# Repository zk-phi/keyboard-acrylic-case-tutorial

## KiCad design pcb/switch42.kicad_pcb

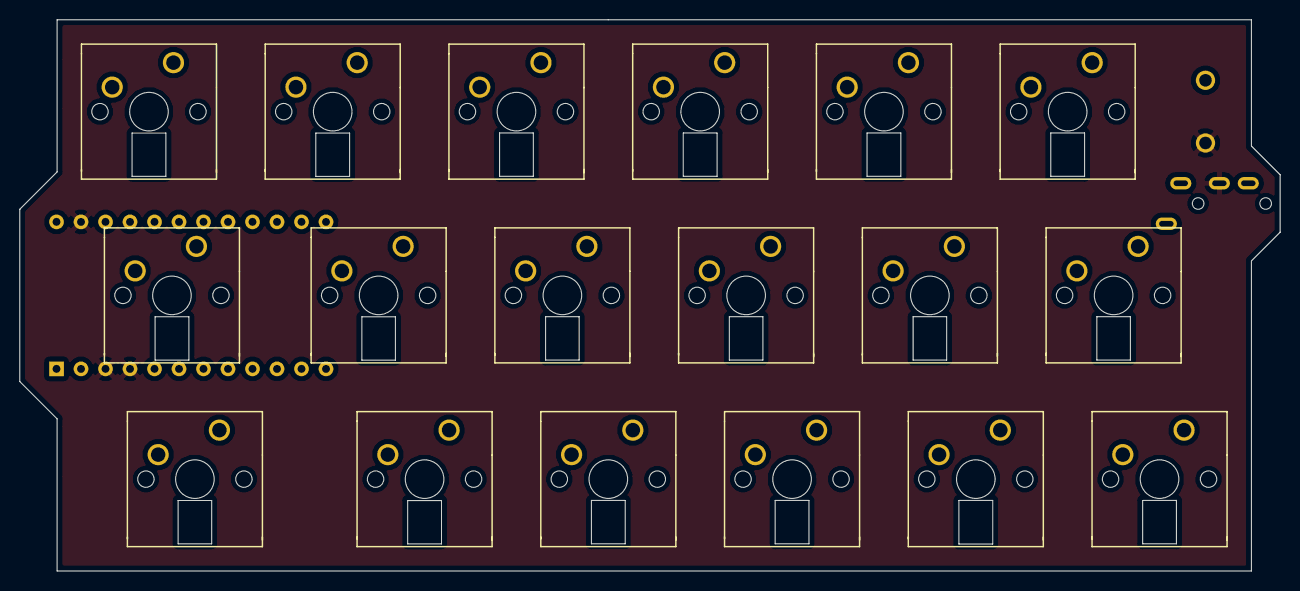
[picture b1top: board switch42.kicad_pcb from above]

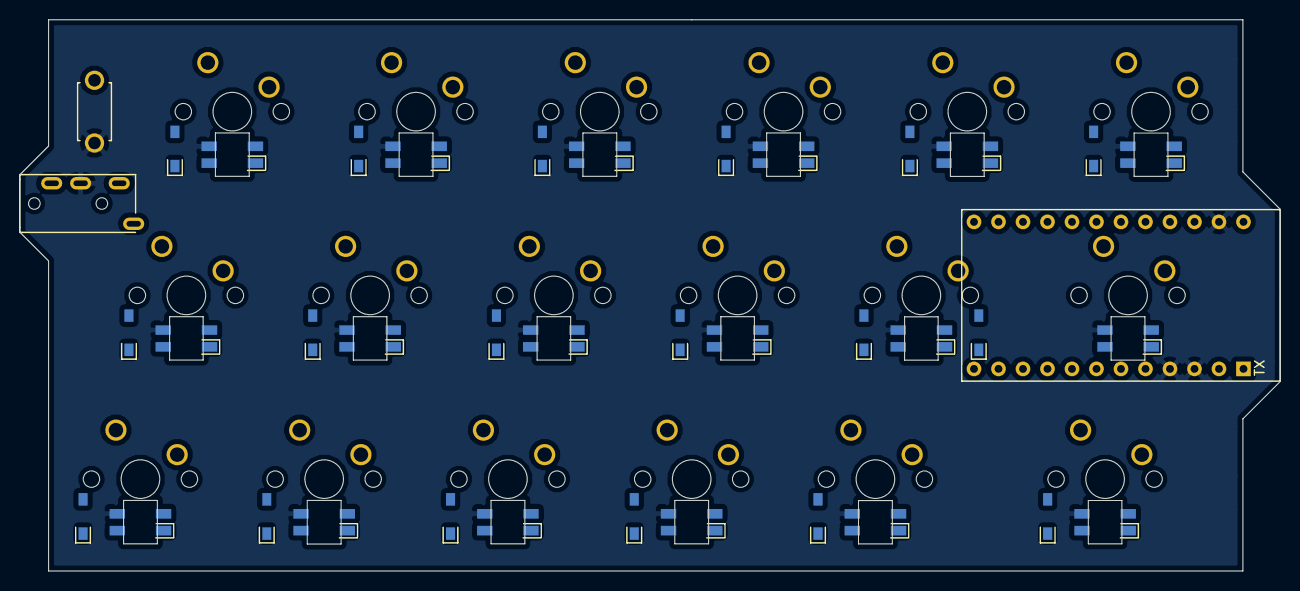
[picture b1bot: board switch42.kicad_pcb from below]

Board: 2 copper layers, 130.7 x 57.1 mm, 57 parts (21 on the bottom side), 49 nets, no tracks yet.

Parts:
D1, D2, D3, D4, D5, D6, D7, D8, D9, D10, D11, D12, D14, D15, D16, D18, D19, D20: D; D_SMD-irreversible
J1: MJ-4PP-9; MJ-4PP-9-irreversible
L1, L2, L3, L4, L5, L6, L7, L8, L9, L10, L11, L12, L14, L15, L16, L18, L19, L20: SK6812MINI; SK6812MINI-irreversible
SW1: SW_PUSH; ResetSW-irreversible
SW2, SW5, SW6, SW7, SW8, SW9, SW10, SW11, SW12, SW13, SW15, SW16, SW17, SW19, SW20, SW21: SW_PUSH; MX_1.00u-irreversible
SW3: SW_PUSH; MX_1.25u-irreversible
SW4: SW_PUSH; MX_1.50u-irreversible
U1: ProMicro; ProMicro_Reversed_Conthrough-irreversible

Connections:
GND: J1.C, L1.2, L2.2, L3.2, L4.2, L5.2, L6.2, L7.2, L8.2, L9.2, L10.2, L11.2, L12.2, L14.2, L15.2, L16.2, L18.2, L19.2, L20.2, SW1.2, U1.3, U1.4, U1.23
unnamed: D1.2, SW2.2
unnamed: D2.2, SW3.2
unnamed: D3.2, SW4.2
unnamed: D4.2, SW5.2
unnamed: D5.2, SW6.2
unnamed: D6.2, SW7.2
unnamed: D7.2, SW8.2
unnamed: D8.2, SW9.2
unnamed: D9.2, SW10.2
unnamed: D10.2, SW11.2
unnamed: D11.2, SW12.2
unnamed: D12.2, SW13.2
unnamed: D14.2, SW15.2
unnamed: D15.2, SW16.2
unnamed: D16.2, SW17.2
unnamed: D18.2, SW19.2
unnamed: D19.2, SW20.2
unnamed: D20.2, SW21.2
unnamed: L1.1, L4.3
unnamed: L2.1, L5.3
unnamed: L3.1, L6.3
unnamed: L4.1, L7.3
unnamed: L5.1, L8.3
unnamed: L6.1, L9.3
unnamed: L10.1, L14.3
unnamed: L7.1, L10.3
unnamed: L11.1, L15.3
unnamed: L8.1, L11.3
unnamed: L12.1, L16.3
unnamed: L9.1, L12.3
unnamed: L14.1, L18.3
unnamed: L15.1, L19.3
unnamed: L16.1, L20.3
unnamed: L2.3, L18.1
unnamed: L3.3, L19.1
VCC: J1.D, L1.4, L2.4, L3.4, L4.4, L5.4, L6.4, L7.4, L8.4, L9.4, L10.4, L11.4, L12.4, L14.4, L15.4, L16.4, L18.4, L19.4, L20.4, U1.21
col0: SW2.1, SW3.1, SW4.1, U1.20
col1: SW5.1, SW6.1, SW7.1, U1.19
col2: SW8.1, SW9.1, SW10.1, U1.18
col3: SW11.1, SW12.1, SW13.1, U1.17
col4: SW15.1, SW16.1, SW17.1, U1.16
col5: SW19.1, SW20.1, SW21.1, U1.15
data: J1.B, U1.2
led: L1.3, U1.1
reset: SW1.1, U1.22
row0: D1.1, D4.1, D7.1, D10.1, D14.1, D18.1, U1.7
row1: D2.1, D5.1, D8.1, D11.1, D15.1, D19.1, U1.8
row2: D3.1, D6.1, D9.1, D12.1, D16.1, D20.1, U1.9

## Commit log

2019-12-06 Add materials
